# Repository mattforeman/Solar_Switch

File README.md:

# Solar Switch

Code compiles in Arduino IDE and layout files open in Eagle.

This was designed as a cheap/easy/hackable method of controlling how solar and AC mains power is routed. By default, this system monitors a solar battery bank voltage,
when it detects that the batteries are low, it switches the load to AC mains to allow the batteries to recharge - at which time it switches back to solar power.

This was mostly designed for hobbyists who have a only a few solar panels and want to power their projects/computers from solar, but do not have a big enough system
to run their load 24/7.

It was designed using the ATMEGA328P in the Arduino IDE and a compatible Arduino shield header. This allows the user to add any number of accesories to the system.
Some of the ideas that I had in mind were: Sd card logging and Wifi/GSM notifications.

The most current iteration is seen here:

Our first Arduino prototype board is seen here:

Board Layout:

Current schematic is seen here:

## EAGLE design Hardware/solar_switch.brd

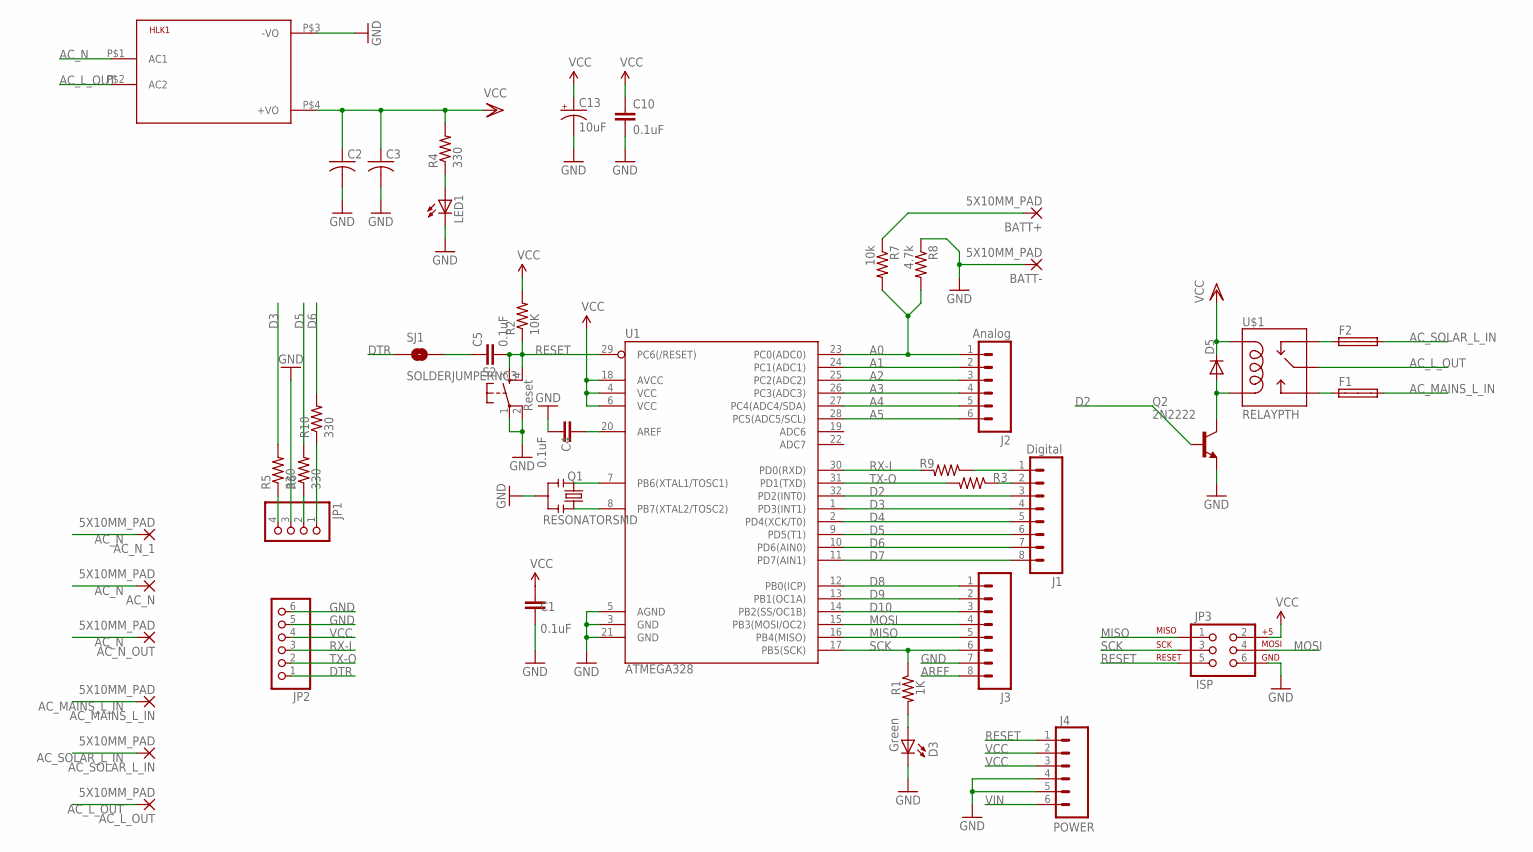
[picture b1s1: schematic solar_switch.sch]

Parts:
AC_L_OUT: 5X10MM_PAD; SMD5-10
AC_MAINS_L_IN: 5X10MM_PAD; SMD5-10
AC_N: 5X10MM_PAD; SMD5-10
AC_N_1: 5X10MM_PAD; SMD5-10
AC_N_OUT: 5X10MM_PAD; SMD5-10
AC_SOLAR_L_IN: 5X10MM_PAD; SMD5-10
BATT+: 5X10MM_PAD; SMD5-10
BATT-: 5X10MM_PAD; SMD5-10
C1, C4, C5, C10: 0.1uF; C0805
C2, C3: C-USC0805K; C0805K
C13: 10uF; PANASONIC_B
D3: Green; CHIP-LED0805
D5: 1N4004; DO41-10
F1, F2: SHKOG
HLK1: HLK-PM013W; HLK-PM01
J1: Digital; 1X08
J2: Analog; 1X06
J3: M081X08; 1X08
J4: POWER; 1X06
JP1: PINHD-1X4; 1X04
JP2: PINHD-1X6; 1X06
JP3: ISP; 2X3
LED1: LEDCHIPLED_0805; CHIPLED_0805
Q1: RESONATORSMD; RESONATOR-SMD
Q2: 2N2222; TO18
R1: 1K; R0805
R2: 10K; R0805
R3, R9: 220; R0805
R4, R5, R6, R10: 330; R0805
R7: 10k; M0805
R8: 4.7k; M0805
S2: Reset; TACTILE_SWITCH_SMD
SJ1: SOLDERJUMPERNC3; SJ_2S-NOTRACE
U1: ATMEGA328; TQFP32-08
U$1: RELAYPTH; SRD-05VDC-SL-C

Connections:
A0: J2.1, R7.2, R8.2, U1.23 (PC0(ADC0))
A1: J2.2, U1.24 (PC1(ADC1))
A2: J2.3, U1.25 (PC2(ADC2))
A3: J2.4, U1.26 (PC3(ADC3))
A4: J2.5, U1.27 (PC4(ADC4/SDA))
A5: J2.6, U1.28 (PC5(ADC5/SCL))
AC_L_OUT: AC_L_OUT.1, HLK1.P$2 (AC2), U$1.SWCOMMON
AC_MAINS_L_IN: AC_MAINS_L_IN.1, F1.2A
AC_N: AC_N.1, AC_N_1.1, AC_N_OUT.1, HLK1.P$1 (AC1)
AC_SOLAR_L_IN: AC_SOLAR_L_IN.1, F2.2A
AREF: C4.2, J3.8, U1.20 (AREF)
D2: J1.3, Q2.2 (B), U1.32 (PD2(INT0))
D3: J1.4, R5.2, U1.1 (PD3(INT1))
D4: J1.5, U1.2 (PD4(XCK/T0))
D5: J1.6, R6.2, U1.9 (PD5(T1))
D6: J1.7, R10.2, U1.10 (PD6(AIN0))
D7: J1.8, U1.11 (PD7(AIN1))
D8: J3.1, U1.12 (PB0(ICP))
D9: J3.2, U1.13 (PB1(OC1A))
D10: J3.3, U1.14 (PB2(SS/OC1B))
DTR: JP2.1, SJ1.1
GND: BATT-.1, C1.1, C2.2, C3.2, C4.1, C10.2, C13.-, D3.C, HLK1.P$3 (-VO), J3.7, J4.4, J4.5, JP1.3, JP2.5, JP2.6, JP3.6, LED1.C, Q1.2, Q2.1 (E), R8.1, S2.1, S2.2, U1.3 (GND), U1.5 (AGND), U1.21 (GND)
MISO: J3.5, JP3.1, U1.16 (PB4(MISO))
MOSI: J3.4, JP3.4, U1.15 (PB3(MOSI/OC2))
unnamed: D3.A, R1.2
unnamed: C5.1, SJ1.2
unnamed: Q1.1, U1.8 (PB7(XTAL2/TOSC2))
unnamed: Q1.3, U1.7 (PB6(XTAL1/TOSC1))
unnamed: LED1.A, R4.1
unnamed: JP1.1, R10.1
unnamed: F2.1A, U$1.SWCLOSED (SWCLOSE)
unnamed: F1.1A, U$1.SWOPEN
unnamed: JP1.4, R5.1
unnamed: JP1.2, R6.1
unnamed: D5.A, Q2.3 (C), U$1.COIL0
unnamed: BATT+.1, R7.1
RESET: C5.2, J4.1, JP3.5, R2.1, S2.3, S2.4, U1.29 (PC6(/RESET))
RX-I: JP2.3, R9.2, U1.30 (PD0(RXD))
RX-IP: J1.2, R3.1
SCK: J3.6, JP3.3, R1.1, U1.17 (PB5(SCK))
TX-O: JP2.2, R3.2, U1.31 (PD1(TXD))
TX-OP: J1.1, R9.1
VCC: C1.2, C2.1, C3.1, C10.1, C13.+, D5.C, HLK1.P$4 (+VO), J4.2, J4.3, JP2.4, JP3.2, R2.2, R4.2, U1.4 (VCC), U1.6 (VCC), U1.18 (AVCC), U$1.COIL1
VIN: J4.6

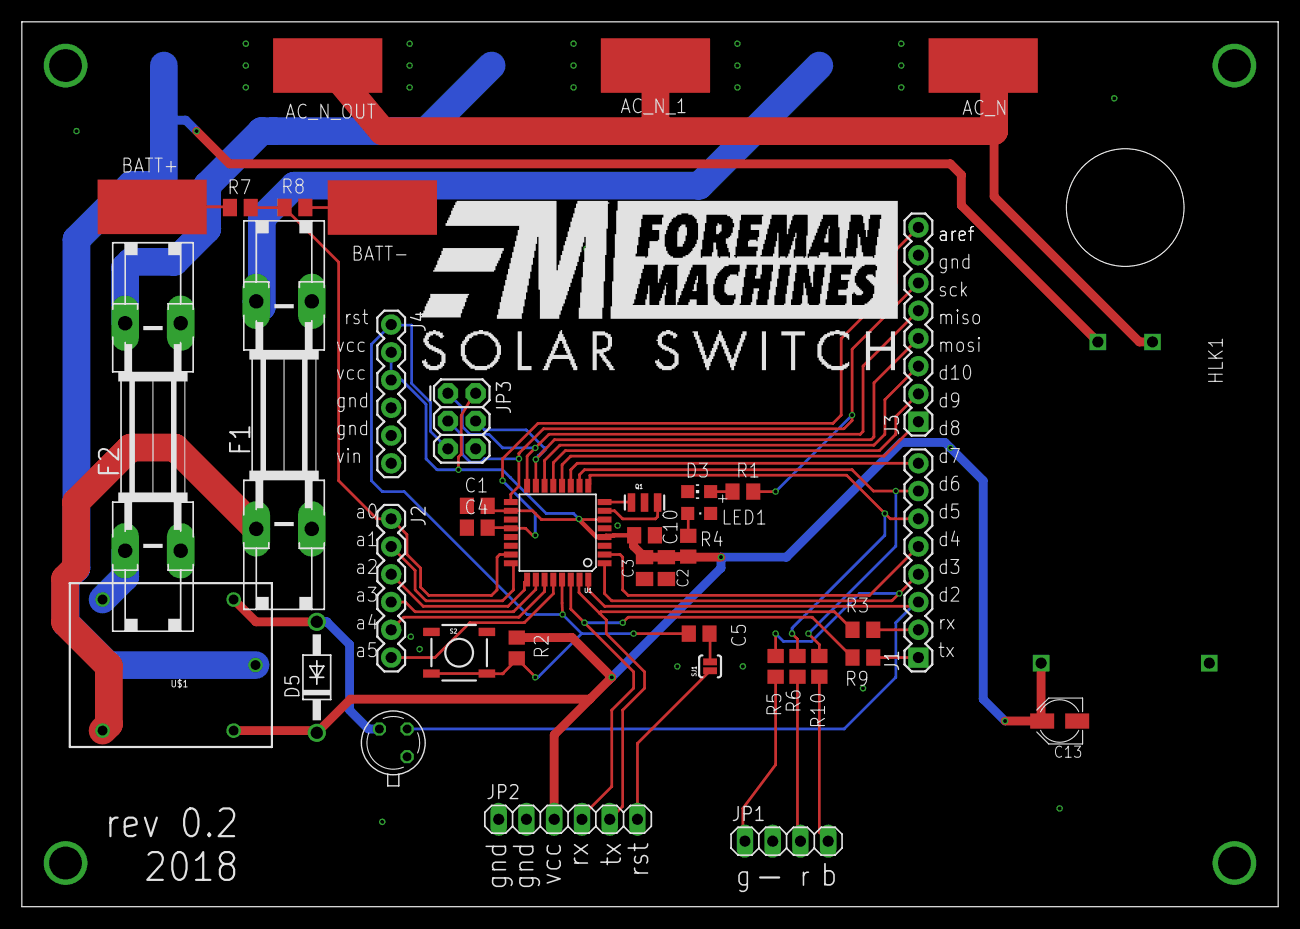
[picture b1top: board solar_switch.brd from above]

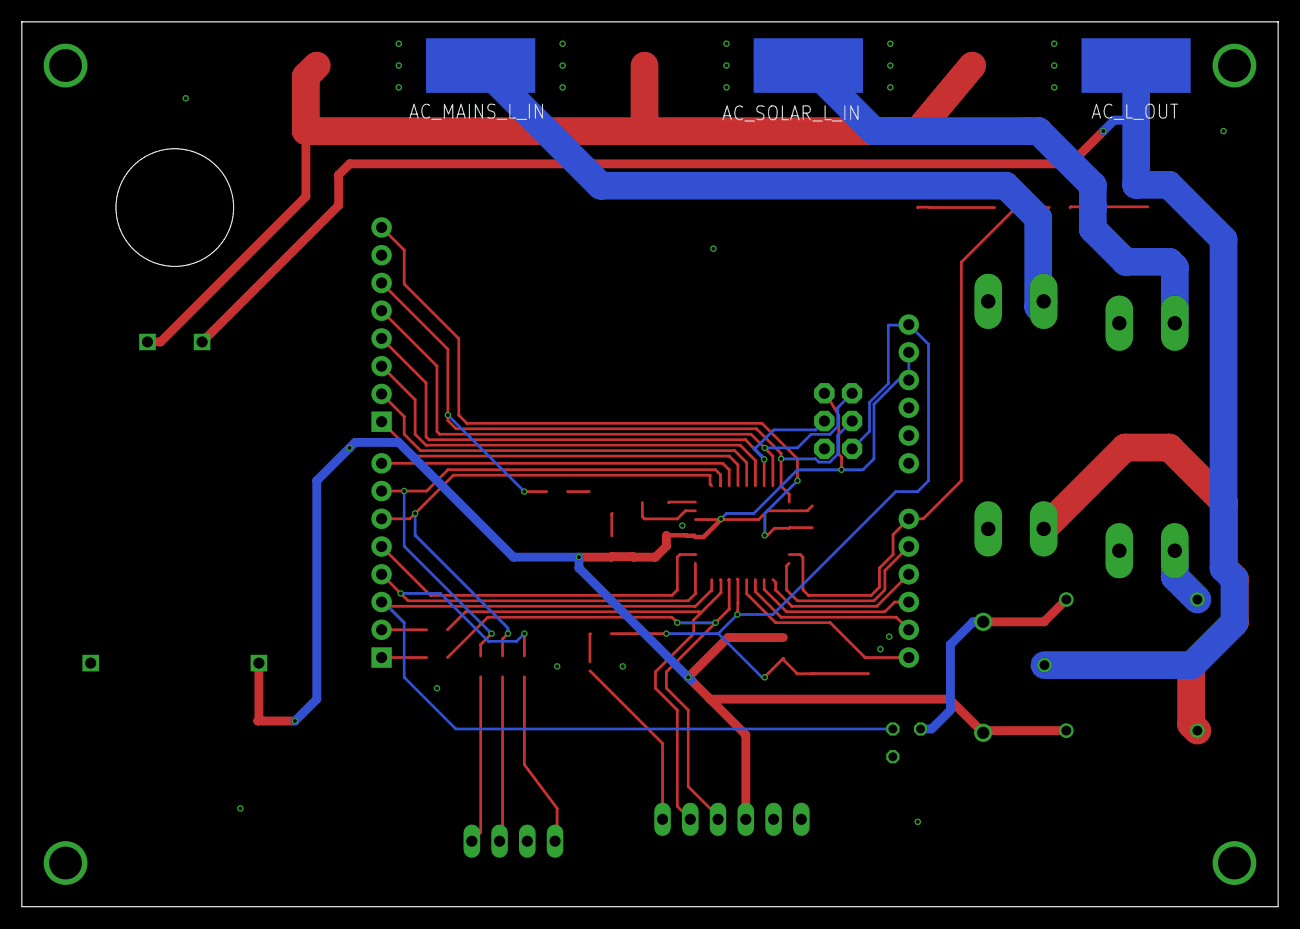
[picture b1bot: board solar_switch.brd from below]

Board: 2 copper layers, 115.0 x 81.0 mm, 44 parts (3 on the bottom side), 43 nets.

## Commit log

2018-10-15 initial push
2018-10-15 upload photos
2018-10-15 upload readme
2018-10-15 photos upload and readme change
2019-02-01 Update README.md
    fix photo tags
2019-02-01 Update Solar_Switch_Arduino_Firmware.ino
    removed unneeded comments
